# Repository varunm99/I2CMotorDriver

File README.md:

# I2CMotorDriver
I2C Based motor driver using ATTiny84

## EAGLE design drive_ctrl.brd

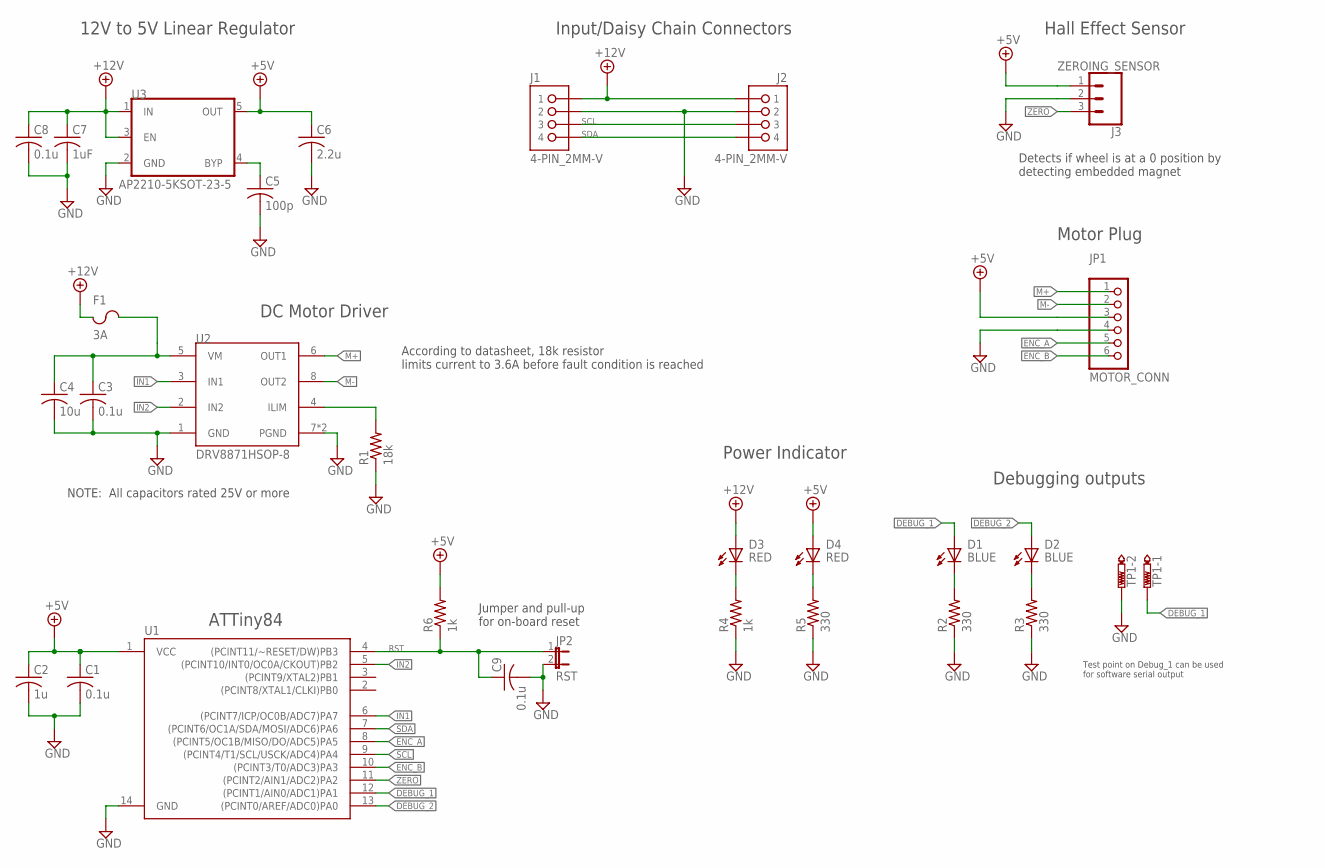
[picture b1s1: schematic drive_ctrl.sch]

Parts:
C1, C3, C8, C9: 0.1u; C0603
C2: 1u; C0603
C4: 10u; C0603
C5: 100p; C0603
C6: 2.2u; C0603
C7: 1uF; C0603
D1, D2: BLUE; CHIP-LED0603
D3, D4: RED; CHIP-LED0603
F1: 3A; F1206
J1, J2: 4-PIN_2MM-V; 2MM-4-V
J3: ZEROING_SENSOR; 1X03
JP1: MOTOR_CONN; 1X06
JP2: RST; JP1
R1: 18k; R0603
R2, R3, R5: 330; R0603
R4, R6: 1k; R0603
TP1: PTR2; P2-38-17
U1: ATTINY84ATTINY84-20PU; DIP14
U2: DRV8871HSOP-8; SOIC127P600X170-9T240X310N
U3: AP2210-5KSOT-23-5; SOT95P282X145-5N

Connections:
12V_FUSE: C3.1, C4.1, F1.2, U2.5 (VM)
+5V: C1.1, C2.1, C6.1, D4.A, J3.1, JP1.3, R6.2, U1.1 (VCC), U3.5 (OUT)
+12V: C7.1, C8.1, D3.A, F1.1, J1.1, J2.1, U3.1 (IN), U3.3 (EN)
BYP: C5.1, U3.4 (BYP)
DEBUG_1: D1.A, TP1.TP-1, U1.12 ((PCINT1/AIN0/ADC1)PA1)
DEBUG_2: D2.A, U1.13 ((PCINT0/AREF/ADC0)PA0)
ENC_A: JP1.5, U1.8 ((PCINT5/OC1B/MISO/DO/ADC5)PA5)
ENC_B: JP1.6, U1.10 ((PCINT3/T0/ADC3)PA3)
GND: C1.2, C2.2, C3.2, C4.2, C5.2, C6.2, C7.2, C8.2, C9.2, J1.2, J2.2, J3.2, JP1.4, JP2.2, R1.1, R2.1, R3.1, R4.1, R5.1, TP1.TP-2, U1.14 (GND), U2.1 (GND), U2.7 (PGND), U2.9 (PGND), U3.2 (GND)
ILIM: R1.2, U2.4 (ILIM)
IN1: U1.6 ((PCINT7/ICP/OC0B/ADC7)PA7), U2.3 (IN1)
IN2: U1.5 ((PCINT10/INT0/OC0A/CKOUT)PB2), U2.2 (IN2)
M+: JP1.1, U2.6 (OUT1)
M-: JP1.2, U2.8 (OUT2)
unnamed: D1.C (K), R2.2
unnamed: D3.C (K), R4.2
unnamed: D2.C (K), R3.2
unnamed: D4.C (K), R5.2
RST: C9.1, JP2.1, R6.1, U1.4 ((PCINT11/~RESET/DW)PB3)
SCL: J1.3, J2.3, U1.9 ((PCINT4/T1/SCL/USCK/ADC4)PA4)
SDA: J1.4, J2.4, U1.7 ((PCINT6/OC1A/SDA/MOSI/ADC6)PA6)
ZERO: J3.3, U1.11 ((PCINT2/AIN1/ADC2)PA2)

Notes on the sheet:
According to datasheet, 18k resistor limits current to 3.6A before fault condition is reached
12V to 5V Linear Regulator
Input/Daisy Chain Connectors
DC Motor Driver
Hall Effect Sensor
Motor Plug
ATTiny84
Debugging outputs
Test point on Debug_1 can be used for software serial output
Power Indicator
Jumper and pull-up for on-board reset
NOTE: All capacitors rated 25V or more
Detects if wheel is at a 0 position by detecting embedded magnet

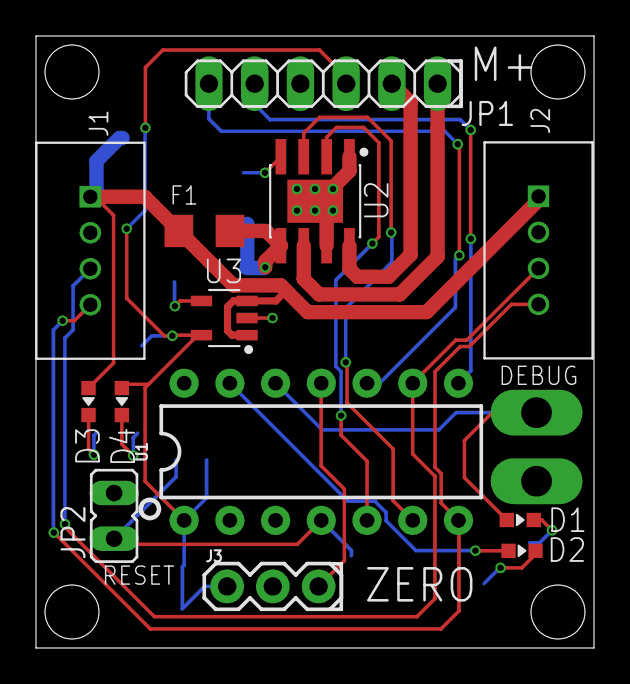
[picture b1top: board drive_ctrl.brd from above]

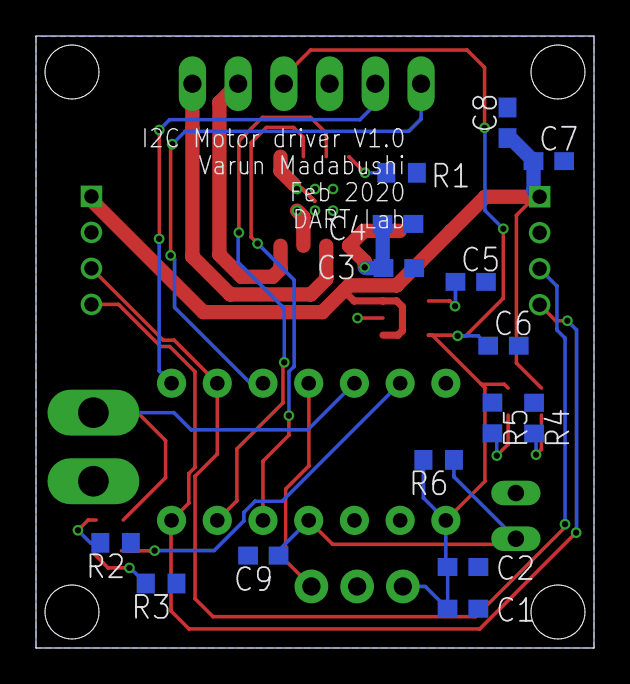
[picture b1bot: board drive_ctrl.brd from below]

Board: 2 copper layers, 31.0 x 34.0 mm, 29 parts (15 on the bottom side), 22 nets.

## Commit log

2020-02-19 Added fuse, decoupling capacitors, and changed routing
2020-02-20 Exported files for Version 1.0
2020-09-01 Added gitignore

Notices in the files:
parts and their libraries:
SparkFun-IC-Microcontroller: Licensing: Creative Commons ShareAlike 4.0 International - https://creativecommons.org/licenses/by-sa/4.0
